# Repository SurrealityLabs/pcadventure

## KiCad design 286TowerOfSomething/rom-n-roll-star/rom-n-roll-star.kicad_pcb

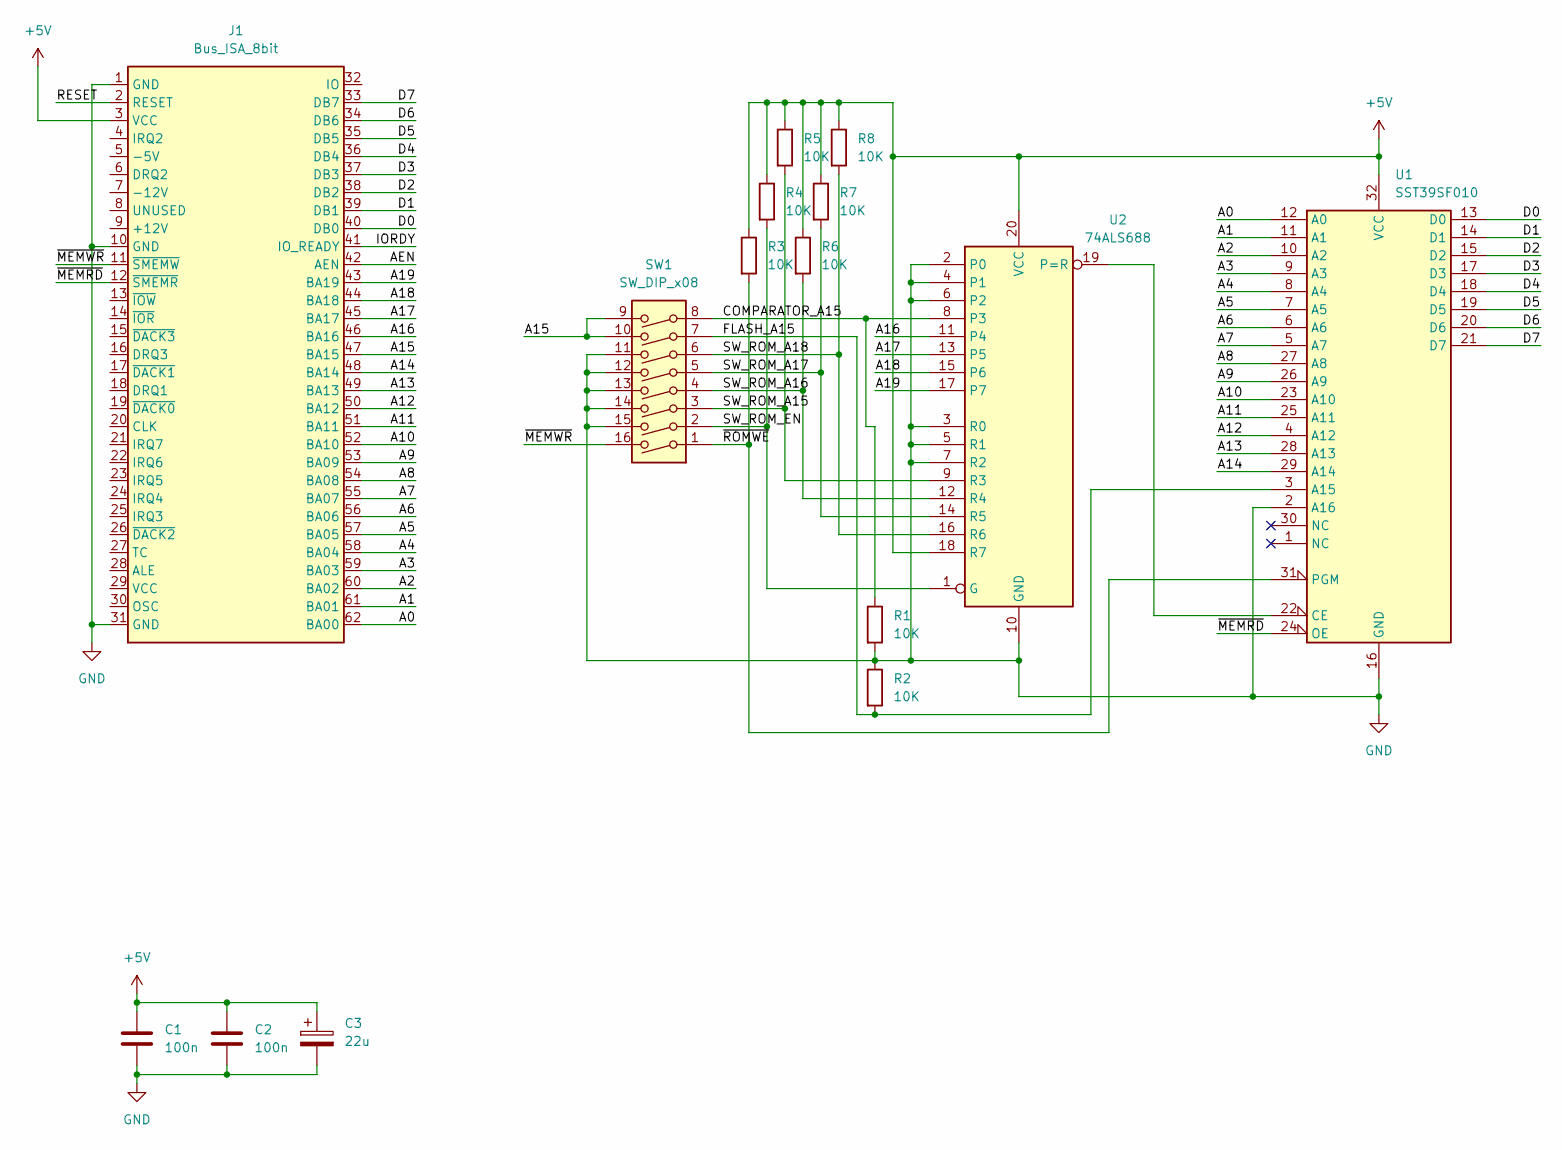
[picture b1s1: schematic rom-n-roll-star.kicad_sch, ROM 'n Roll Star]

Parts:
C1, C2: 100n; C_0603_1608Metric_Pad1.08x0.95mm_HandSolder
C3: 22u; CP_Elec_5x5.3
J1: Bus_ISA_8bit; BUS_AT_8BIT
R1, R2, R3, R4, R5, R6, R7, R8: 10K; R_0603_1608Metric_Pad0.98x0.95mm_HandSolder
SW1: SW_DIP_x08; SW_DIP_SPSTx08_Slide_9.78x22.5mm_W7.62mm_P2.54mm
U1: SST39SF010; DIP-32_W15.24mm
U2: 74ALS688; DIP-20_W7.62mm

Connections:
+5V: C1.1, C2.1, C3.1, J1.3 (VCC), R3.1, R4.1, R5.1, R6.1, R7.1, R8.1, U1.32 (VCC), U2.18 (R7), U2.20 (VCC)
/A0: J1.62 (BA00), U1.12 (A0)
/A1: J1.61 (BA01), U1.11 (A1)
/A2: J1.60 (BA02), U1.10 (A2)
/A3: J1.59 (BA03), U1.9 (A3)
/A4: J1.58 (BA04), U1.8 (A4)
/A5: J1.57 (BA05), U1.7 (A5)
/A6: J1.56 (BA06), U1.6 (A6)
/A7: J1.55 (BA07), U1.5 (A7)
/A8: J1.54 (BA08), U1.27 (A8)
/A9: J1.53 (BA09), U1.26 (A9)
/A10: J1.52 (BA10), U1.23 (A10)
/A11: J1.51 (BA11), U1.25 (A11)
/A12: J1.50 (BA12), U1.4 (A12)
/A13: J1.49 (BA13), U1.28 (A13)
/A14: J1.48 (BA14), U1.29 (A14)
/A15: J1.47 (BA15), SW1.9, SW1.10
/A16: J1.46 (BA16), U2.11 (P4)
/A17: J1.45 (BA17), U2.13 (P5)
/A18: J1.44 (BA18), U2.15 (P6)
/A19: J1.43 (BA19), U2.17 (P7)
/AEN: J1.42 (AEN)
/COMPARATOR_A15: R1.1, SW1.8, U2.8 (P3)
/D0: J1.40 (DB0), U1.13 (D0)
/D1: J1.39 (DB1), U1.14 (D1)
/D2: J1.38 (DB2), U1.15 (D2)
/D3: J1.37 (DB3), U1.17 (D3)
/D4: J1.36 (DB4), U1.18 (D4)
/D5: J1.35 (DB5), U1.19 (D5)
/D6: J1.34 (DB6), U1.20 (D6)
/D7: J1.33 (DB7), U1.21 (D7)
/FLASH_A15: R2.2, SW1.7, U1.3 (A15)
/IORDY: J1.41 (IO_READY)
/RESET: J1.2 (RESET)
/SW_ROM_A15: R5.2, SW1.3, U2.9 (R3)
/SW_ROM_A16: R6.2, SW1.4, U2.12 (R4)
/SW_ROM_A17: R7.2, SW1.5, U2.14 (R5)
/SW_ROM_A18: R8.2, SW1.6, U2.16 (R6)
/SW_ROM_EN: R4.2, SW1.2, U2.1 (G)
/~MEMRD: J1.12 (~SMEMR), U1.24 (OE)
/~MEMWR: J1.11 (~SMEMW), SW1.16
/~ROMWE: R3.2, SW1.1, U1.31 (PGM)
GND: C1.2, C2.2, C3.2, J1.1 (GND), J1.10 (GND), J1.31 (GND), R1.2, R2.1, SW1.11, SW1.12, SW1.13, SW1.14, SW1.15, U1.2 (A16), U1.16 (GND), U2.2 (P0), U2.3 (R0), U2.4 (P1), U2.5 (R1), U2.6 (P2), U2.7 (R2), U2.10 (GND)
unnamed: U1.22 (CE), U2.19 (P=R)

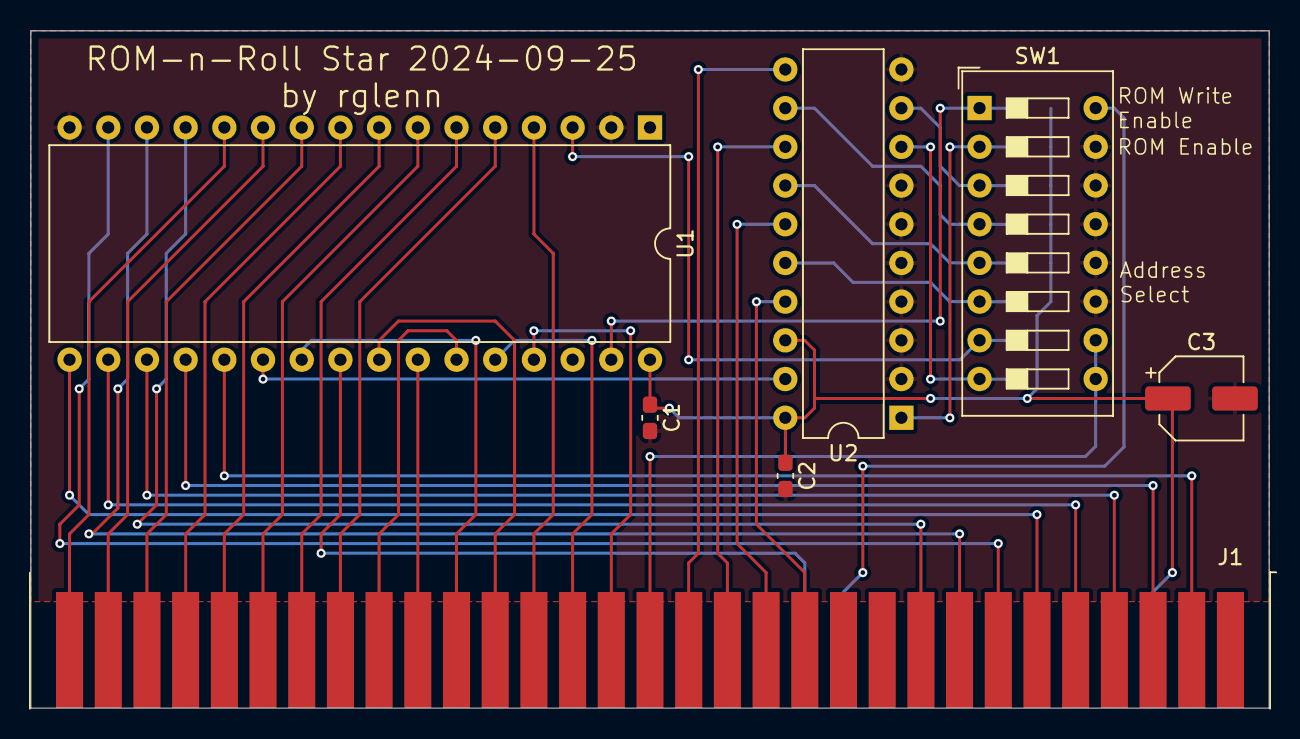
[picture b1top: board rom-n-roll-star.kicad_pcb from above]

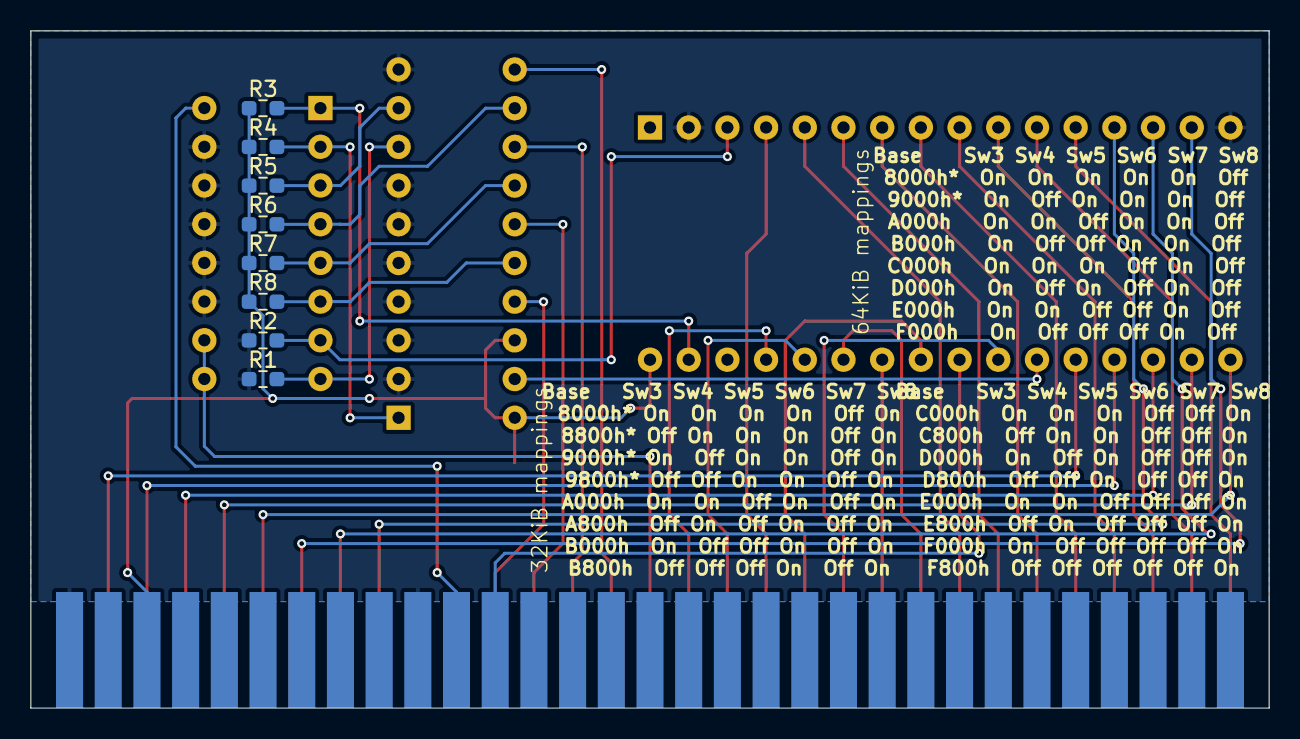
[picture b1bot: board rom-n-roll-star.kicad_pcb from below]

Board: 2 copper layers, 81.3 x 44.4 mm, 15 parts (8 on the bottom side), 41 nets.

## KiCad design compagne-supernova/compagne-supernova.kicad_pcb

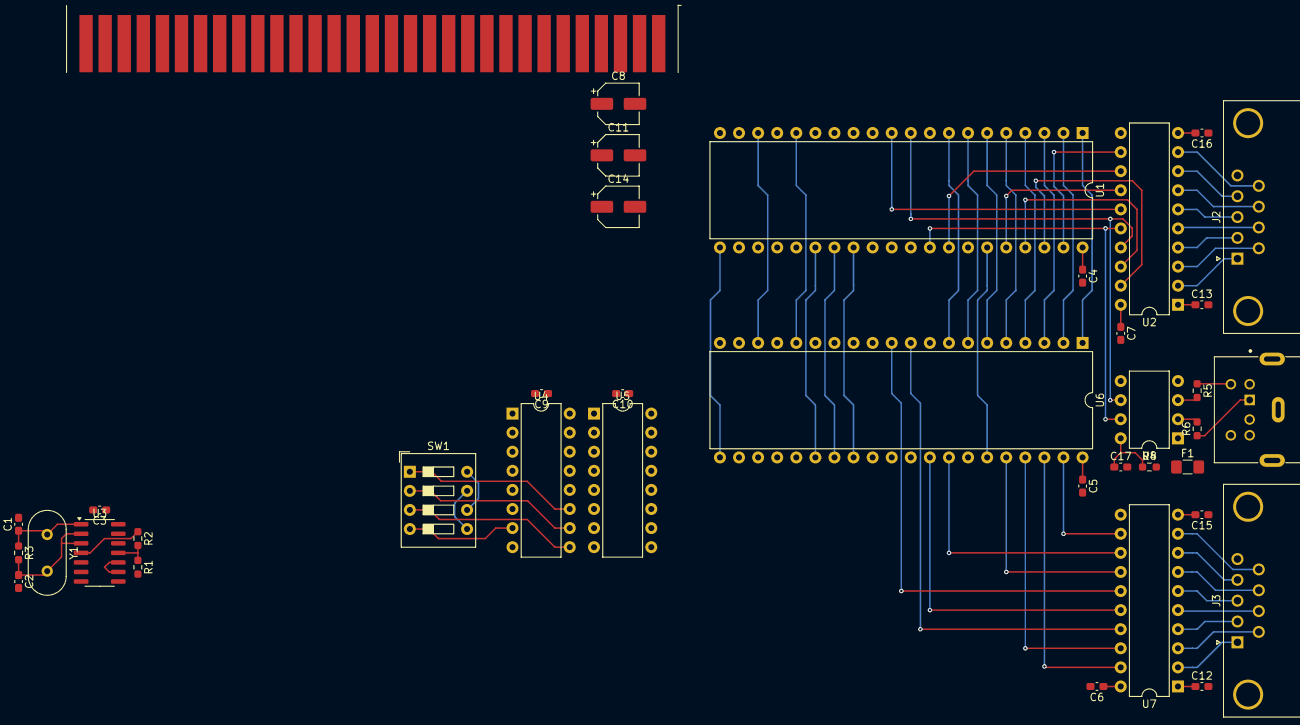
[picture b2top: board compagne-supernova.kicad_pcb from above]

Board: 2 copper layers, 38 parts (0 on the bottom side), 81 nets.

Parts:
C1, C2: 22p; C_0603_1608Metric_Pad1.08x0.95mm_HandSolder
C3, C4, C5, C6, C7, C9, C10, C12, C13, C15, C16, C17: 100n; C_0603_1608Metric_Pad1.08x0.95mm_HandSolder
C8, C11, C14: 22u; CP_Elec_5x5.3
F1: Fuse; Fuse_1206_3216Metric_Pad1.42x1.75mm_HandSolder
J1: Bus_ISA_8bit; BUS_AT_8BIT
J2, J3: DE9; DSUB-9_Male_Horizontal_P2.77x2.84mm_EdgePinOffset7.70mm_Hou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
J4: Mini-DIN-6; CUI_MD-60SGK
R1, R4: 10K; R_0603_1608Metric_Pad0.98x0.95mm_HandSolder
R2: 1K; R_0603_1608Metric_Pad0.98x0.95mm_HandSolder
R3: 1M; R_0603_1608Metric_Pad0.98x0.95mm_HandSolder
R5, R6: 100; R_0603_1608Metric_Pad0.98x0.95mm_HandSolder
SW1: SW_DIP_x04; SW_DIP_SPSTx04_Slide_9.78x12.34mm_W7.62mm_P2.54mm
U1, U6: 16550; DIP-40_W15.24mm
U2, U7: GD75232N; DIP-20_W7.62mm
U3: 74HCU04; SO-14_3.9x8.65mm_P1.27mm
U4, U5: 74LS138; DIP-16_W7.62mm
U8: ATtiny85-20P; DIP-8_W7.62mm
Y1: 1.8432MHz; Crystal_HC49-U_Vertical

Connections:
+5V: C3.1, C4.1, C5.1, C6.1, C7.1, C8.1, C9.1, C10.1, C17.1, F1.1, J1.3 (VCC), J1.29 (VCC), R4.1, U1.12 (CS0), U1.13 (CS1), U1.40 (VCC), U2.20 (V_{CC}), U3.14 (VCC), U4.16 (VCC), U5.6 (E3), U5.16 (VCC), U6.12 (CS0), U6.13 (CS1), U6.40 (VCC), U7.20 (V_{CC}), U8.8 (VCC)
+12V: C11.1, C12.1, C13.1, J1.9 (+12V), U2.1 (V_{DD}), U7.1 (V_{DD})
-12V: C14.2, C15.2, C16.2, J1.7 (-12V), U2.10 (V_{SS}), U7.10 (V_{SS})
/A0: J1.62 (BA00), U1.28 (A0), U6.28 (A0)
/A1: J1.61 (BA01), U1.27 (A1), U6.27 (A1)
/A2: J1.60 (BA02), U1.26 (A2), U6.26 (A2)
/A3: J1.59 (BA03), U4.3 (A2)
/A4: J1.58 (BA04), U4.2 (A1)
/A5: J1.57 (BA05), U5.3 (A2)
/A6: J1.56 (BA06), U5.2 (A1)
/A7: J1.55 (BA07), U5.1 (A0)
/A8: J1.54 (BA08), U4.1 (A0)
/A9: J1.53 (BA09), U4.6 (E3)
/AEN: J1.42 (AEN), U4.4 (E1)
/CLK_UART: R1.2, U1.16 (XIN), U3.8, U6.16 (XIN)
/D0: J1.40 (DB0), U1.1 (D0), U6.1 (D0)
/D1: J1.39 (DB1), U1.2 (D1), U6.2 (D1)
/D2: J1.38 (DB2), U1.3 (D2), U6.3 (D2)
/D3: J1.37 (DB3), U1.4 (D3), U6.4 (D3)
/D4: J1.36 (DB4), U1.5 (D4), U6.5 (D4)
/D5: J1.35 (DB5), U1.6 (D5), U6.6 (D5)
/D6: J1.34 (DB6), U1.7 (D6), U6.7 (D6)
/D7: J1.33 (DB7), U1.8 (D7), U6.8 (D7)
/IRQ3: J1.25 (IRQ3), U6.30 (INTR)
/IRQ4: J1.24 (IRQ4), U1.30 (INTR)
/PS2 to Serial/PS2_CLK: R5.2, U8.3 (XTAL2/PB4)
/PS2 to Serial/PS2_DAT: R6.2, U8.2 (XTAL1/PB3)
/RESET: J1.2 (RESET), U1.35 (MR), U6.35 (MR)
/RX: U1.10 (SIN), U2.17 (RY3), U8.6 (PB1)
/~0x2E8: SW1.1, U4.11 (O4)
/~0x2F8: SW1.3, U4.9 (O6)
/~0x3E8: SW1.2, U4.10 (O5)
/~0x3F8: SW1.4, U4.7 (O7)
/~IOR: J1.14 (~IOR), U1.21 (~RD), U6.21 (~RD)
/~IOW: J1.13 (~IOW), U1.18 (~WR), U6.18 (~WR)
/~RTS: U1.32 (~RTS), U2.16 (DA1), U8.7 (PB2)
/~UART1_CS: SW1.5, SW1.7, U1.14 (~CS2)
/~UART2_CS: SW1.6, SW1.8, U6.14 (~CS2)
GND: C1.2, C2.2, C3.2, C4.2, C5.2, C6.2, C7.2, C8.2, C9.2, C10.2, C11.2, C12.2, C13.2, C14.1, C15.1, C16.1, C17.2, J1.1 (GND), J1.10 (GND), J1.31 (GND), J2.0 (PAD), J2.5, J3.0 (PAD), J3.5, J4.3, J4.7, U1.19 (WR), U1.20 (GND), U1.22 (RD), U1.25 (~ADS), U2.11 (GND), U3.5, U3.7 (GND), U3.13, U4.8 (GND), U5.4 (E1), U5.5 (E2), U5.8 (GND), U6.19 (WR), U6.20 (GND), U6.22 (RD), U6.25 (~ADS), U7.11 (GND), U8.4 (GND)
unnamed: C1.1, R3.1, U3.1, Y1.1
unnamed: C2.1, R3.2, U3.2, U3.3, Y1.2
unnamed: F1.2, J4.4
unnamed: J4.1, R6.1
unnamed: J4.5, R5.1
unnamed: R1.1, R2.2, U3.11
unnamed: R2.1, U3.4
unnamed: U1.9 (RCLK), U1.15 (~BAUDOUT)
unnamed: U1.11 (SOUT), U2.15 (DA2)
unnamed: U1.36 (~CTS), U2.14 (RY4)
unnamed: U1.38 (~DCD), U2.19 (RY1)
unnamed: U1.37 (~DSR), U2.18 (RY2)
unnamed: U1.33 (~DTR), U2.13 (DA3)
unnamed: U1.39 (~RI), U2.12 (RY5)
unnamed: J2.7, U2.5 (DY1)
unnamed: J2.3, U2.6 (DY2)
unnamed: J2.4, U2.8 (DY3)
unnamed: J2.1, U2.2 (RA1)
unnamed: J2.6, U2.3 (RA2)
unnamed: J2.2, U2.4 (RA3)
unnamed: J2.8, U2.7 (RA4)
unnamed: J2.9, U2.9 (RA5)
unnamed: U3.9, U3.10
unnamed: U4.5 (E2), U5.7 (O7)
unnamed: U6.9 (RCLK), U6.15 (~BAUDOUT)
unnamed: U6.10 (SIN), U7.17 (RY3)
unnamed: U6.11 (SOUT), U7.15 (DA2)
unnamed: U6.36 (~CTS), U7.14 (RY4)
unnamed: U6.38 (~DCD), U7.19 (RY1)
unnamed: U6.37 (~DSR), U7.18 (RY2)
unnamed: U6.33 (~DTR), U7.13 (DA3)
unnamed: U6.39 (~RI), U7.12 (RY5)
unnamed: U6.32 (~RTS), U7.16 (DA1)
unnamed: J3.7, U7.5 (DY1)
unnamed: J3.3, U7.6 (DY2)
unnamed: J3.4, U7.8 (DY3)
unnamed: J3.1, U7.2 (RA1)
unnamed: J3.6, U7.3 (RA2)
unnamed: J3.2, U7.4 (RA3)
unnamed: J3.8, U7.7 (RA4)
unnamed: J3.9, U7.9 (RA5)
unnamed: R4.2, U8.1 (~RESET/PB5)

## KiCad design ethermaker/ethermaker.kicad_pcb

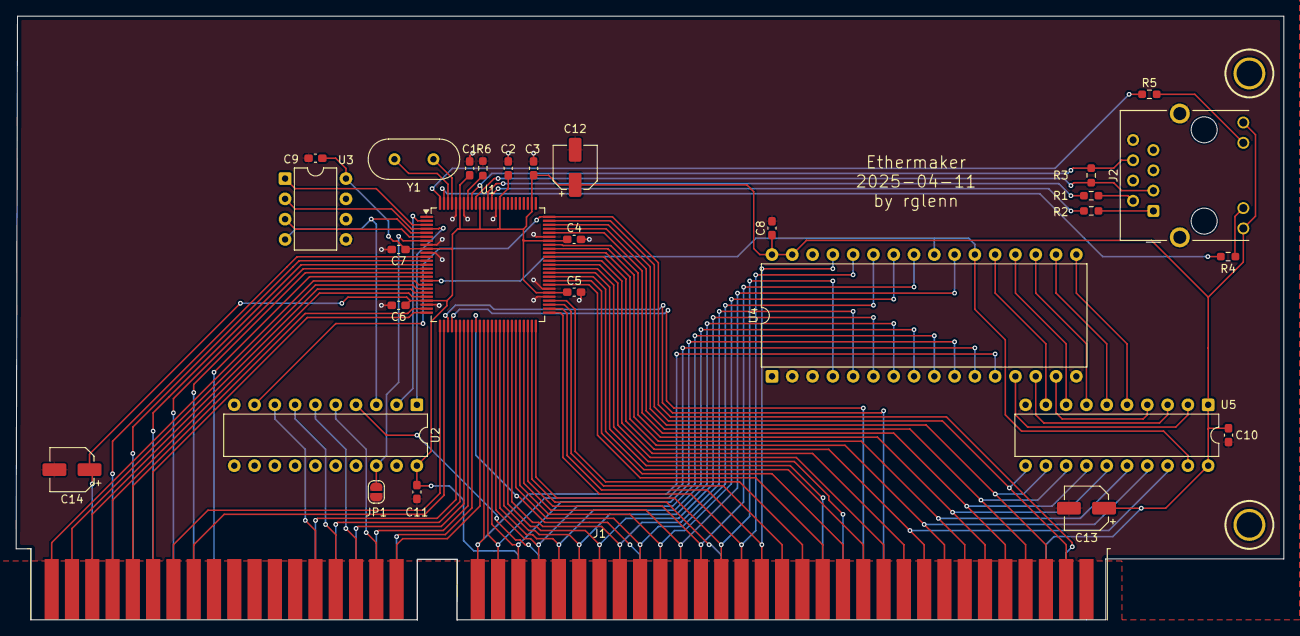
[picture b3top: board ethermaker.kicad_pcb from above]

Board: 2 copper layers, 158.7 x 75.6 mm, 30 parts (0 on the bottom side), 92 nets.

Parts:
BRACKET1: PC_BRACKET_ISA_KEYSTONE_9202_Rev1
C1, C2, C3, C4, C5, C6, C7, C8, C9, C10, C11: 100n; C_0603_1608Metric_Pad1.08x0.95mm_HandSolder
C12, C13, C14: 22u; CP_Elec_5x5.3
J1: Bus_ISA_16bit; BUS_AT
J2: RJ45_Hanrun_HR911105A_Horizontal
JP1: NO_ROM; SolderJumper-2_P1.3mm_Open_RoundedPad1.0x1.5mm
R1, R2: 24.3; R_0603_1608Metric_Pad0.98x0.95mm_HandSolder
R3: 100; R_0603_1608Metric_Pad0.98x0.95mm_HandSolder
R4, R5: 330; R_0603_1608Metric_Pad0.98x0.95mm_HandSolder
R6: 4.99K; R_0603_1608Metric_Pad0.98x0.95mm_HandSolder
U1: CS8900A; LQFP-100_14x14mm_P0.5mm
U2: GAL16V8; DIP-20_W7.62mm
U3: 93C46A; DIP-8_W7.62mm
U4: SST39SF010; DIP-32_W15.24mm
U5: 74LS245; DIP-20_W7.62mm
Y1: 20.0 MHz; Crystal_HC49-4H_Vertical

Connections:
+5V: C1.1, C2.1, C3.1, C4.1, C5.1, C6.1, C7.1, C8.1, C9.1, C10.1, C11.1, C12.1, C13.1, C14.1, J1.3 (+5V), J1.29 (VCC), J1.78 (+5V), J2.9, J2.12, U1.9 (DVDD), U1.22 (DVDD), U1.56 (DVDD), U1.69 (DVDD), U1.77 (~SLEEP), U1.85 (AVDD), U1.90 (AVDD), U1.95 (AVDD), U2.20 (VCC), U3.8 (VCC), U4.31 (PGM), U4.32 (VCC), U5.1 (A->B), U5.20 (VCC)
/A0: J1.62 (BA00), U1.37 (SA0), U4.12 (A0)
/A1: J1.61 (BA01), U1.38 (SA1), U4.11 (A1)
/A2: J1.60 (BA02), U1.39 (SA2), U4.10 (A2)
/A3: J1.59 (BA03), U1.40 (SA3), U4.9 (A3)
/A4: J1.58 (BA04), U1.41 (SA4), U4.8 (A4)
/A5: J1.57 (BA05), U1.42 (SA5), U4.7 (A5)
/A6: J1.56 (BA06), U1.43 (SA6), U4.6 (A6)
/A7: J1.55 (BA07), U1.44 (SA7), U4.5 (A7)
/A8: J1.54 (BA08), U1.45 (SA8), U4.27 (A8)
/A9: J1.53 (BA09), U1.46 (SA9), U4.26 (A9)
/A10: J1.52 (BA10), U1.47 (SA10), U4.23 (A10)
/A11: J1.51 (BA11), U1.48 (SA11), U4.25 (A11)
/A12: J1.50 (BA12), U1.50 (SA12), U4.4 (A12)
/A13: J1.49 (BA13), U1.51 (SA13), U4.28 (A13)
/A14: J1.48 (BA14), U1.52 (SA14), U4.29 (A14)
/A15: J1.47 (BA15), U1.53 (SA15)
/A16: J1.46 (BA16), U1.54 (SA16)
/A17: J1.45 (BA17), U1.58 (SA17)
/A18: J1.44 (BA18), U1.59 (SA18)
/A19: J1.43 (BA19), U1.60 (SA19)
/AEN: J1.42 (AEN), U1.63 (AEN)
/BALE: J1.28 (ALE), U2.4 (I4)
/D0: J1.40 (DB0), U1.65 (SD0), U5.18 (B0)
/D1: J1.39 (DB1), U1.66 (SD1), U5.17 (B1)
/D2: J1.38 (DB2), U1.67 (SD2), U5.16 (B2)
/D3: J1.37 (DB3), U1.68 (SD3), U5.15 (B3)
/D4: J1.36 (DB4), U1.71 (SD4), U5.14 (B4)
/D5: J1.35 (DB5), U1.72 (SD5), U5.13 (B5)
/D6: J1.34 (DB6), U1.73 (SD6), U5.12 (B6)
/D7: J1.33 (DB7), U1.74 (SD7), U5.11 (B7)
/D8: J1.91 (D8), U1.27 (SD8)
/D9: J1.92 (D9), U1.26 (SD9)
/D10: J1.93 (D10), U1.25 (SD10)
/D11: J1.94 (D11), U1.24 (SD11)
/D12: J1.95 (D12), U1.21 (SD12)
/D13: J1.96 (D13), U1.20 (SD13)
/D14: J1.97 (D14), U1.19 (SD14)
/D15: J1.98 (D15), U1.18 (SD15)
/DRQ5: J1.73 (DRQ5), U1.15 (DMARQ0)
/DRQ6: J1.75 (DRQ6), U1.13 (DMARQ1)
/DRQ7: J1.77 (DRQ7), U1.11 (DMARQ2)
/EEDIN: U1.6 (EEDataIn), U3.3 (DI)
/EEDOUT: U1.5 (EEDataOut), U2.3 (I3), U3.4 (DO)
/EE_CS: U1.3 (EECS), U3.1 (CS)
/EE_SK: U1.4 (EESK), U2.1 (I1/CLK), U3.2 (SCLK)
/IOCHRDY: J1.41 (IO_READY), U1.64 (IOCHRDY)
/IRQ5: J1.23 (IRQ5), U1.35 (INTRQ3)
/IRQ10: J1.65 (IRQ10), U1.32 (INTRQ0)
/IRQ11: J1.66 (IRQ11), U1.31 (INTRQ1)
/IRQ12: J1.67 (IRQ12), U1.30 (INTRQ2)
/LA20: J1.85 (LA20), U2.8 (I8)
/LA21: J1.84 (LA21), U2.7 (I7)
/LA22: J1.83 (LA22), U2.6 (I6)
/LA23: J1.82 (LA23), U2.5 (I5)
/RESET: J1.2 (RESET), U1.75 (RESET), U2.9 (I9)
/ROM_CS: U1.17 (~CSOUT), U4.22 (CE), U4.24 (OE), U5.19 (CE)
/~CHIPSEL: JP1.1 (A), U1.7 (~CHIPSEL), U2.18 (IO2)
/~DACK5: J1.72 (~DACK5), U1.16 (~DMACK0)
/~DACK6: J1.74 (~DACK6), U1.14 (~DMACK1)
/~DACK7: J1.76 (~DACK7), U1.12 (~DMACK2)
/~EL_CS: U1.2 (~ELCS), U2.2 (I2)
/~IOCS16: J1.64 (~IOCS16), U1.33 (~IOCS16)
/~IOR: J1.14 (~IOR), U1.61 (~IOR)
/~IOW: J1.13 (~IOW), U1.62 (~IOW)
/~MEMCS16: J1.63 (~MEMCS16), U1.34 (~MEMCS16)
/~REFRESH: J1.19 (~REFRESH), U1.49 (~REFRESH)
/~SBHE: J1.81 (SBHE), U1.36 (~SBHE)
/~SMEMR: J1.12 (~SMEMR), U1.29 (~MEMR)
/~SMEMW: J1.11 (~SMEMW), U1.28 (~MEMW)
GND: C1.2, C2.2, C3.2, C4.2, C5.2, C6.2, C7.2, C8.2, C9.2, C10.2, C11.2, C12.2, C13.2, C14.2, J1.1 (GND), J1.10 (GND), J1.31 (GND), J1.80 (GND), J2.8, J2.SH, JP1.2 (B), R6.2, U1.1 (AVSS), U1.8 (DVSS), U1.10 (DVSS), U1.23 (DVSS), U1.55 (DVSS), U1.57 (DVSS), U1.70 (DVSS), U1.86 (AVSS), U1.89 (AVSS), U1.94 (AVSS), U1.96 (AVSS), U2.10 (GND), U2.11 (I10/~OE), U3.5 (GND), U4.2 (A16), U4.3 (A15), U4.16 (GND), U5.10 (GND)
unnamed: J2.10, R4.2
unnamed: J2.11, R5.2
unnamed: J2.3 (RD+), R3.2, U1.91 (RXD+)
unnamed: J2.6 (RD-), R3.1, U1.92 (RXD-)
unnamed: J2.1 (TD+), R2.2
unnamed: J2.2 (TD-), R1.2
unnamed: R6.1, U1.93 (RES)
unnamed: R2.1, U1.87 (TXD+)
unnamed: R1.1, U1.88 (TXD-)
unnamed: U1.97 (XTAL1), Y1.1
unnamed: U1.98 (XTAL2), Y1.2
unnamed: R5.1, U1.100 (~LANLED)
unnamed: R4.1, U1.99 (~LINKLED)
unnamed: U4.13 (D0), U5.2 (A0)
unnamed: U4.14 (D1), U5.3 (A1)
unnamed: U4.15 (D2), U5.4 (A2)
unnamed: U4.17 (D3), U5.5 (A3)
unnamed: U4.18 (D4), U5.6 (A4)
unnamed: U4.19 (D5), U5.7 (A5)
unnamed: U4.20 (D6), U5.8 (A6)
unnamed: U4.21 (D7), U5.9 (A7)

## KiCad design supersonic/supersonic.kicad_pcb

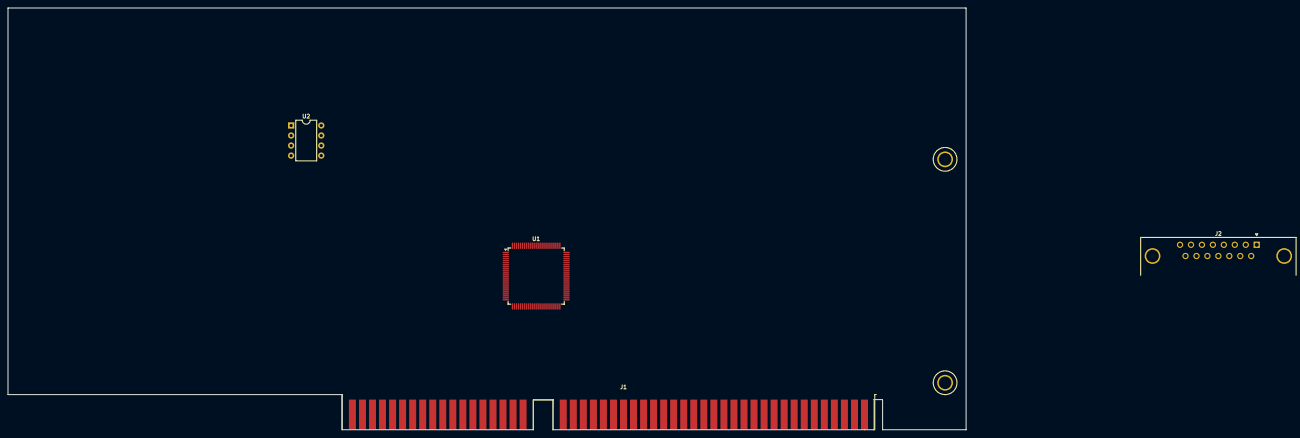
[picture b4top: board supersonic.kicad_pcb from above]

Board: 2 copper layers, 242.4 x 106.7 mm, 5 parts (0 on the bottom side), 56 nets, no tracks yet.

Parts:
BRACKET1: PC_BRACKET_ISA_KEYSTONE_9202_Rev1
J1: Bus_ISA_16bit; BUS_AT
J2: DA15_Receptacle_MountingHoles; DSUB-15_Female_Horizontal_P2.77x2.84mm_EdgePinOffset4.94mm_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
U1: CS4237B; LQFP-100_14x14mm_P0.5mm
U2: 24LC04; DIP-8_W7.62mm

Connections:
+5V: J1.3 (+5V), J1.29 (VCC), J1.78 (+5V), U1.45 (VD1), U2.8 (VCC)
/+5FILT: J2.1, J2.8, J2.9, U1.17 (VDF1), U1.54 (VDF4), U1.65 (VDF2), U1.98 (VDF3)
/A0: J1.62 (BA00), U1.25 (SA0)
/A1: J1.61 (BA01), U1.26 (SA1)
/A2: J1.60 (BA02), U1.27 (SA2)
/A3: J1.59 (BA03), U1.28 (SA3)
/A4: J1.58 (BA04), U1.29 (SA4)
/A5: J1.57 (BA05), U1.30 (SA5)
/A6: J1.56 (BA06), U1.31 (SA6)
/A7: J1.55 (BA07), U1.32 (SA7)
/A8: J1.54 (BA08), U1.33 (SA8)
/A9: J1.53 (BA09), U1.34 (SA9)
/A10: J1.52 (BA10), U1.35 (SA10)
/A11: J1.51 (BA11), U1.36 (SA11)
/A12: J1.50 (BA12), U1.94 (SA12/~CDCS)
/A13: J1.49 (BA13), U1.93 (SA13/~CDACK/~MCS)
/A14: J1.48 (BA14), U1.92 (SA14/CDINT)
/A15: J1.47 (BA15), U1.91 (SA15/CDRQ/~MNT)
/AEN: J1.42 (AEN), U1.39 (AEN)
/D0: J1.40 (DB0), U1.41 (SD0)
/D1: J1.39 (DB1), U1.42 (SD1)
/D2: J1.38 (DB2), U1.43 (SD2)
/D3: J1.37 (DB3), U1.44 (SD3)
/D4: J1.36 (DB4), U1.47 (SD4)
/D5: J1.35 (DB5), U1.48 (SD5)
/D6: J1.34 (DB6), U1.49 (SD6)
/D7: J1.33 (DB7), U1.50 (SD7)
/DRQ0: J1.71 (DRQ0), U1.55 (DRQA)
/DRQ1: J1.18 (DRQ1), U1.51 (DRQB)
/DRQ3: J1.16 (DRQ3), U1.52 (DRQC)
/IOCHRDY: J1.41 (IO_READY), U1.40 (IOCHRDY)
/IRQ5: J1.23 (IRQ5), U1.24 (IRQA)
/IRQ7: J1.21 (IRQ7), U1.23 (IRQB)
/IRQ9: J1.4 (IRQ2), U1.22 (IRQC)
/IRQ11: J1.66 (IRQ11), U1.21 (IRQD)
/IRQ12: J1.67 (IRQ12), U1.20 (IRQE)
/IRQ15: J1.68 (IRQ15), U1.19 (IRQF)
/JAB1: J2.2, U1.70 (JAB1)
/JAB2: J2.7, U1.61 (JAB2)
/JACX: J2.3, U1.68 (JACX)
/JACY: J2.6, U1.63 (JACY)
/JBB1: J2.10, U1.69 (JBB1/FSYNC)
/JBB2: J2.14, U1.62 (JBB2/SCLK)
/JBCX: J2.11 (P111), U1.67 (JBCX/SDOUT)
/JBCY: J2.13, U1.64 (JBCY/SDIN)
/MIDIN: J2.15, U1.59 (MIDIN)
/MIDOUT: J2.12, U1.60 (MIDOUT)
/RESET: J1.2 (RESET), U1.90 (RESDRV)
/SCL: U1.14 (SCL/XA0), U2.6 (SCL)
/SDA: U1.8 (XD0/SDA), U2.5 (SDA)
/~DACK0: J1.70 (~DACK0), U1.58 (~DACKA)
/~DACK1: J1.17 (~DACK1), U1.56 (~DACKB)
/~DACK3: J1.15 (~DACK3), U1.57 (~DACKC)
/~IOR: J1.14 (~IOR), U1.37 (~IOR)
/~IOW: J1.13 (~IOW), U1.38 (~IOW)
GND: J1.1 (GND), J1.10 (GND), J1.31 (GND), J1.80 (GND), J2.0 (PAD), J2.4, J2.5, U1.18 (SGND), U1.46 (DGND), U1.53 (SGND), U1.66 (SGND), U1.71 (TEST), U1.97 (SGND), U2.1 (A0), U2.2 (A1), U2.3 (A2), U2.4 (GND), U2.7 (WP)

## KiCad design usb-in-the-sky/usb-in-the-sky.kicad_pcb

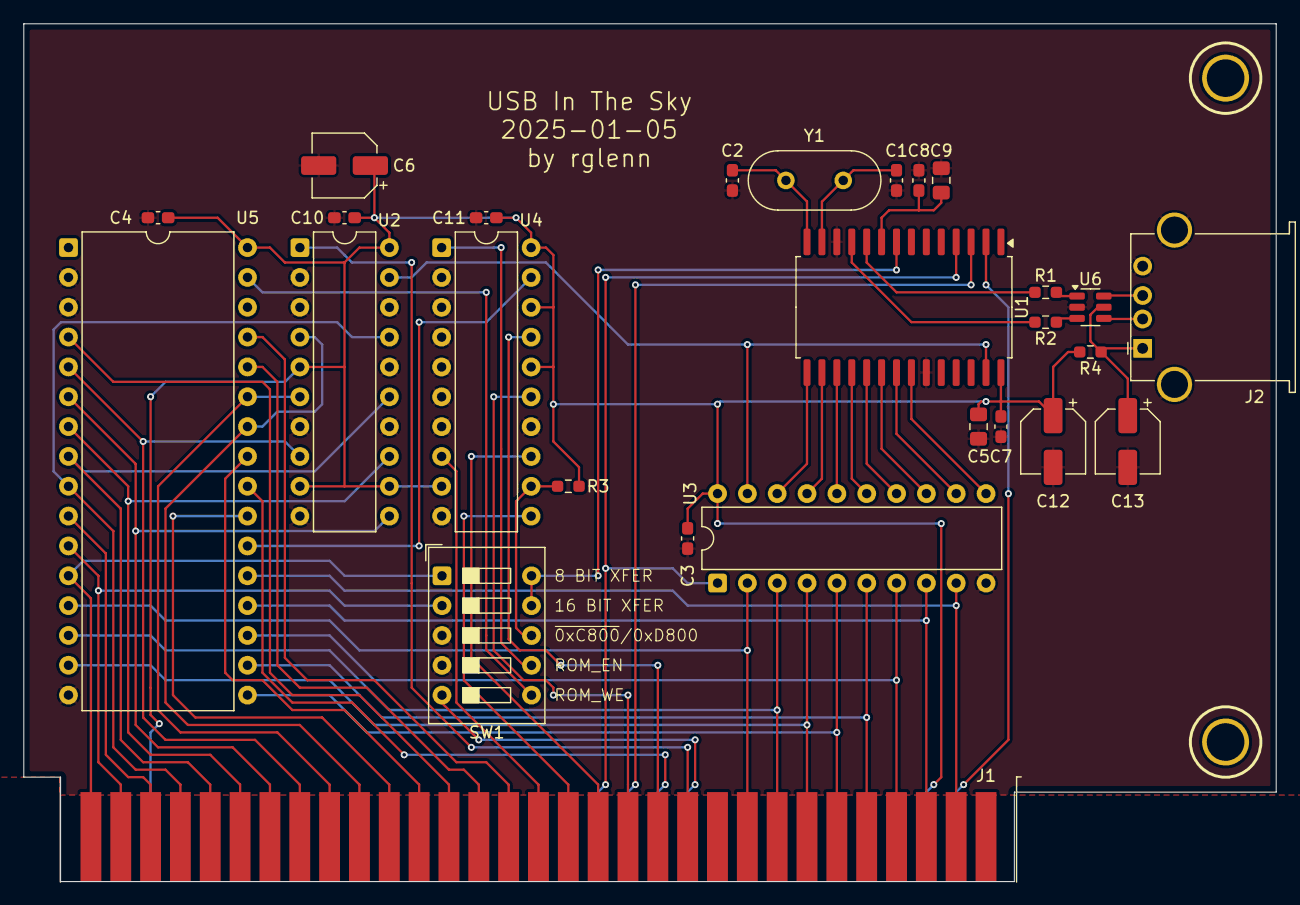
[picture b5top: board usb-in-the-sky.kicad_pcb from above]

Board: 2 copper layers, 106.6 x 73.0 mm, 28 parts (0 on the bottom side), 60 nets.

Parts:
BRACKET1: PC_BRACKET_ISA_KEYSTONE_9202_Rev1
C1, C2: 15p; C_0603_1608Metric_Pad1.08x0.95mm_HandSolder
C3, C4, C7, C8, C10, C11: 100n; C_0603_1608Metric_Pad1.08x0.95mm_HandSolder
C5, C9: 1u; C_0805_2012Metric_Pad1.18x1.45mm_HandSolder
C6: 22u; CP_Elec_5x5.3
C12, C13: 100u; CP_Elec_5x5.3
J1: Bus_ISA_8bit; BUS_AT_8BIT
J2: USB_A; USB_A_Stewart_SS-52100-001_Horizontal
R1, R2: 22; R_0603_1608Metric_Pad0.98x0.95mm_HandSolder
R3: 10K; R_0603_1608Metric_Pad0.98x0.95mm_HandSolder
R4: 2; R_0603_1608Metric_Pad0.98x0.95mm_HandSolder
SW1: SW_DIP_x05; SW_DIP_SPSTx05_Slide_9.78x14.88mm_W7.62mm_P2.54mm
U1: CH375; SOP-28_8.4x18.16mm_P1.27mm
U2: 74LS688; DIP-20_W7.62mm
U3: 74LS245; DIP-20_W7.62mm
U4: 74ALS688; DIP-20_W7.62mm
U5: SST39SF010; DIP-32_W15.24mm
U6: USBLC6-2SC6; SOT-23-6
Y1: 12 MHz; Crystal_HC49-U_Vertical

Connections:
+5V: C3.1, C4.1, C5.1, C6.1, C7.1, C10.1, C11.1, C12.1, J1.3 (VCC), J1.29 (VCC), R3.1, R4.1, U1.28 (VCC), U2.5 (R1), U2.9 (R3), U2.12 (R4), U2.20 (VCC), U3.20 (VCC), U4.9 (R3), U4.16 (R6), U4.18 (R7), U4.20 (VCC), U5.32 (VCC)
/A0: J1.62 (BA00), SW1.1, U5.12 (A0)
/A0_CFG: SW1.9, SW1.10, U1.8 (A0)
/A1: J1.61 (BA01), SW1.2, U5.11 (A1)
/A2: J1.60 (BA02), U5.10 (A2)
/A3: J1.59 (BA03), U2.17 (P7), U5.9 (A3)
/A4: J1.58 (BA04), U2.15 (P6), U5.8 (A4)
/A5: J1.57 (BA05), U2.13 (P5), U5.7 (A5)
/A6: J1.56 (BA06), U2.11 (P4), U5.6 (A6)
/A7: J1.55 (BA07), U2.8 (P3), U5.5 (A7)
/A8: J1.54 (BA08), U2.6 (P2), U5.27 (A8)
/A9: J1.53 (BA09), U2.4 (P1), U5.26 (A9)
/A10: J1.52 (BA10), U5.23 (A10)
/A11: J1.51 (BA11), U5.25 (A11)
/A12: J1.50 (BA12), U5.4 (A12)
/A13: J1.49 (BA13), U5.28 (A13)
/A14: J1.48 (BA14), U5.29 (A14)
/A15: J1.47 (BA15), U4.8 (P3)
/A16: J1.46 (BA16), U4.11 (P4)
/A17: J1.45 (BA17), U4.13 (P5)
/A18: J1.44 (BA18), U4.15 (P6)
/A19: J1.43 (BA19), U4.17 (P7)
/AEN: J1.42 (AEN), U2.1 (G)
/D0: J1.40 (DB0), U3.2 (A0), U5.13 (D0)
/D1: J1.39 (DB1), U3.3 (A1), U5.14 (D1)
/D2: J1.38 (DB2), U3.4 (A2), U5.15 (D2)
/D3: J1.37 (DB3), U3.5 (A3), U5.17 (D3)
/D4: J1.36 (DB4), U3.6 (A4), U5.18 (D4)
/D5: J1.35 (DB5), U3.7 (A5), U5.19 (D5)
/D6: J1.34 (DB6), U3.8 (A6), U5.20 (D6)
/D7: J1.33 (DB7), U3.9 (A7), U5.21 (D7)
/RESET: J1.2 (RESET), U1.2 (RSTI)
/SW_ROM_EN: SW1.7, U4.1 (G)
/~IOR: J1.14 (~IOR), U1.4 (~RD), U3.1 (A->B)
/~IOW: J1.13 (~IOW), U1.3 (~WR)
/~MEMRD: J1.12 (~SMEMR), U5.24 (OE)
/~MEMWR: J1.11 (~SMEMW), SW1.5
/~ROMWE: SW1.6, U5.31 (PGM)
/~USB_CS: U1.27 (~CS), U2.19 (P=R), U3.19 (CE)
GND: C1.2, C2.2, C3.2, C4.2, C5.2, C6.2, C7.2, C8.2, C9.2, C10.2, C11.2, C12.2, C13.2, J1.1 (GND), J1.10 (GND), J1.31 (GND), J2.4 (GND), J2.5 (Shield), SW1.3, SW1.4, U1.12 (GND), U1.23 (GND), U2.2 (P0), U2.3 (R0), U2.7 (R2), U2.10 (GND), U2.14 (R5), U2.16 (R6), U2.18 (R7), U3.10 (GND), U4.2 (P0), U4.3 (R0), U4.4 (P1), U4.5 (R1), U4.6 (P2), U4.7 (R2), U4.10 (GND), U4.14 (R5), U5.2 (A16), U5.3 (A15), U5.16 (GND), U6.2 (GND)
unnamed: J2.3 (D+), U6.6 (I/O1)
unnamed: J2.2 (D-), U6.4 (I/O2)
unnamed: C13.1, J2.1 (VBUS), R4.2, U6.5 (VBUS)
unnamed: R1.2, U6.1 (I/O1)
unnamed: R2.2, U6.3 (I/O2)
unnamed: U1.15 (D0), U3.18 (B0)
unnamed: U1.16 (D1), U3.17 (B1)
unnamed: U1.17 (D2), U3.16 (B2)
unnamed: U1.18 (D3), U3.15 (B3)
unnamed: U1.19 (D4), U3.14 (B4)
unnamed: U1.20 (D5), U3.13 (B5)
unnamed: U1.21 (D6), U3.12 (B6)
unnamed: U1.22 (D7), U3.11 (B7)
unnamed: R1.1, U1.10 (UD+)
unnamed: R2.1, U1.11 (UD-)
unnamed: C8.1, C9.1, U1.9 (V3)
unnamed: C1.1, U1.13 (XI), Y1.1
unnamed: C2.1, U1.14 (XO), Y1.2
unnamed: U4.19 (P=R), U5.22 (CE)
unnamed: R3.2, SW1.8, U4.12 (R4)
